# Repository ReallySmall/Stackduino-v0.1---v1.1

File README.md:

Stackduino
==========
Please visit the project site for details: https://www.stackduino.net

Copyright 2017 Richard Iles

Permission is hereby granted, free of charge, to any person obtaining a copy of this software and associated documentation files (the "Software"), to deal in the Software without restriction, including without limitation the rights to use, copy, modify, merge, publish, distribute, sublicense, and/or sell copies of the Software, and to permit persons to whom the Software is furnished to do so, subject to the following conditions:

The above copyright notice and this permission notice shall be included in all copies or substantial portions of the Software.

THE SOFTWARE IS PROVIDED "AS IS", WITHOUT WARRANTY OF ANY KIND, EXPRESS OR IMPLIED, INCLUDING BUT NOT LIMITED TO THE WARRANTIES OF MERCHANTABILITY, FITNESS FOR A PARTICULAR PURPOSE AND NONINFRINGEMENT. IN NO EVENT SHALL THE AUTHORS OR COPYRIGHT HOLDERS BE LIABLE FOR ANY CLAIM, DAMAGES OR OTHER LIABILITY, WHETHER IN AN ACTION OF CONTRACT, TORT OR OTHERWISE, ARISING FROM, OUT OF OR IN CONNECTION WITH THE SOFTWARE OR THE USE OR OTHER DEALINGS IN THE SOFTWARE.

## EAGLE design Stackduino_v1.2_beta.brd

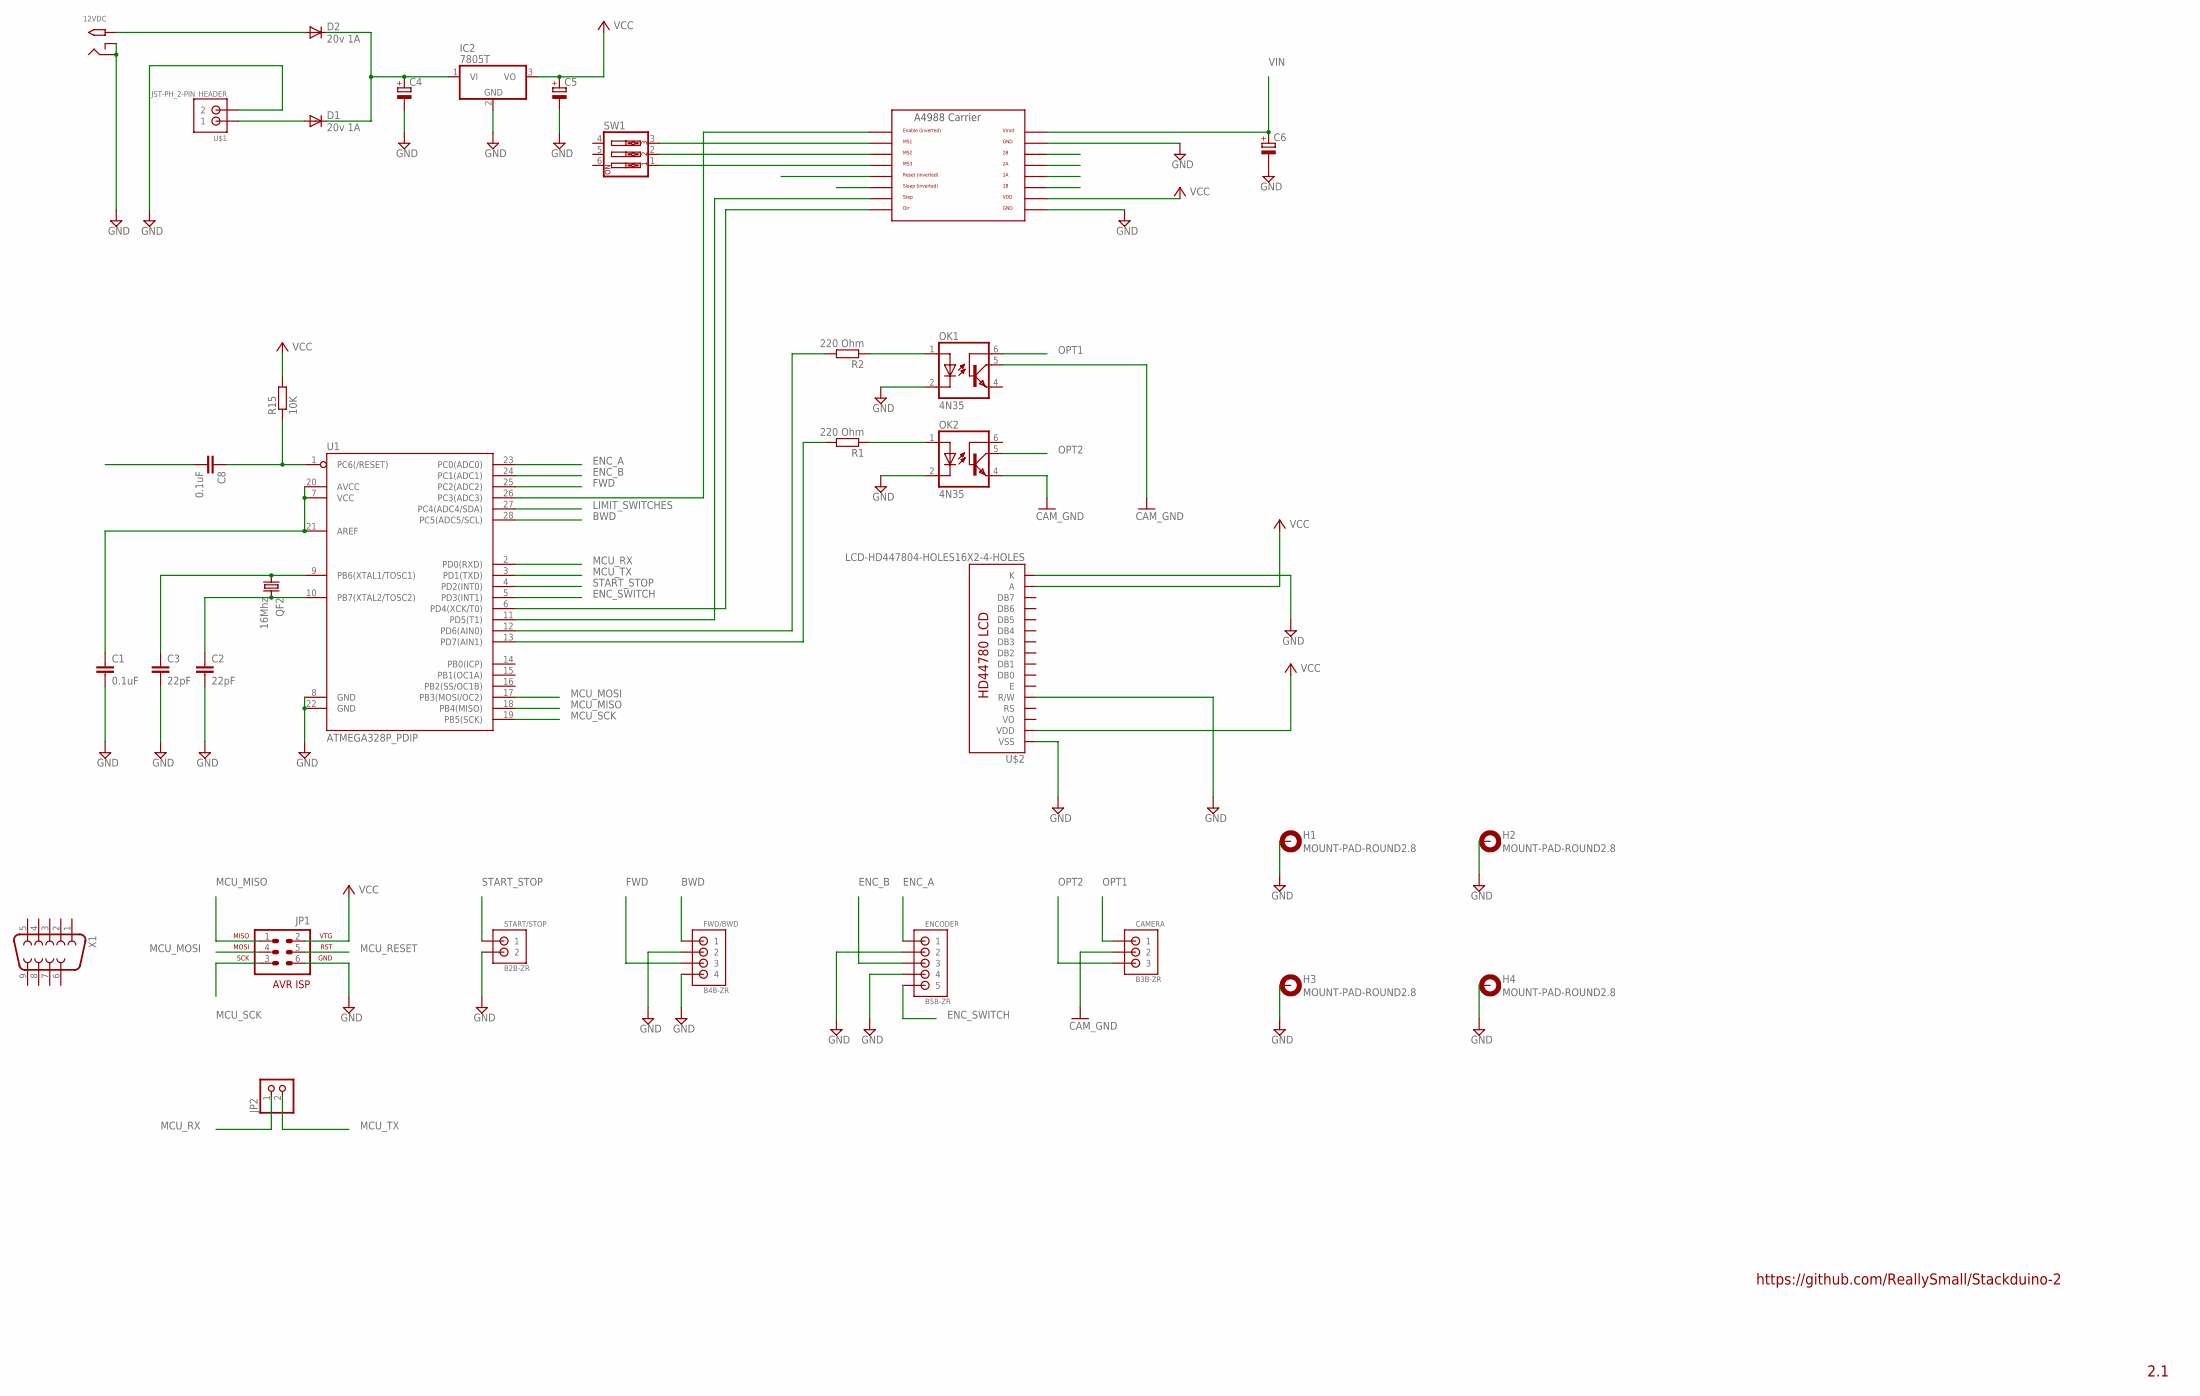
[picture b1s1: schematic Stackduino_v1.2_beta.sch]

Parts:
12VDC: 2.1MMJACKTHM; PJ-102A
A4988_CARRIER: A4988BREAKOUT
C1, C8: 0.1uF; C025-030X050
C2, C3: 22pF; C025-030X050
C4, C5, C6: CPOL-EUSANYO_C; SANYO-OSCON_C
CAMERA: B3B-ZR
D1, D2: 20v 1A; DO41-10
ENCODER: B5B-ZR
FWD/BWD: B4B-ZR
H1, H2, H3, H4: MOUNT-PAD-ROUND2.8; 2,8-PAD
IC2: 7805T; TO220H
JP1: AVR-5_AVR-ISP-6
JP2: PINHD-1X2; 1X02
OK1, OK2: 4N35; DIL06
QF2: 16Mhz; HC49U-V
R1, R2: 220 Ohm; 0207/10
R15: 10K; 0207/10
START/STOP: B2B-ZR
SW1: SW_DIP-3; EDG-03
U1: ATMEGA328P_PDIP; DIL28-3
U$1: JST-PH_2-PIN_HEADER; JST_B2B-PH_HEADER
U$2: LCD-HD447804-HOLES16X2-4-HOLES; LCD-16X2-4HOLES
X1: F09H

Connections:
BWD: FWD/BWD.1, U1.28 (PC5(ADC5/SCL))
CAM_GND: CAMERA.2, OK1.5 (COL), OK2.4 (EMI)
DIR: A4988_CARRIER.DIR, U1.6 (PD4(XCK/T0))
ENABLE: A4988_CARRIER.EN, U1.26 (PC3(ADC3))
ENC_A: ENCODER.1, U1.23 (PC0(ADC0))
ENC_B: ENCODER.3, U1.24 (PC1(ADC1))
ENC_SWITCH: ENCODER.5, U1.5 (PD3(INT1))
FWD: FWD/BWD.3, U1.25 (PC2(ADC2))
GND: 12VDC.RING, 12VDC.RING_SW, A4988_CARRIER.GND, A4988_CARRIER.GND@0 (GND), C1.2, C2.2, C3.2, C4.-, C5.-, C6.-, ENCODER.2, ENCODER.4, FWD/BWD.2, FWD/BWD.4, H1.B2,8, H2.B2,8, H3.B2,8, H4.B2,8, IC2.2 (GND), JP1.6, OK1.2 (C), OK2.2 (C), START/STOP.2, U1.8 (GND), U1.22 (GND), U$1.P2 (2), U$2.1 (VSS), U$2.5 (R/W), U$2.16 (K)
LIMIT_SWITCHES: U1.27 (PC4(ADC4/SDA))
MCU_MISO: JP1.1, U1.18 (PB4(MISO))
MCU_MOSI: JP1.4, U1.17 (PB3(MOSI/OC2))
MCU_RESET: C8.1, JP1.5, R15.1, U1.1 (PC6(/RESET))
MCU_RX: JP2.1, U1.2 (PD0(RXD))
MCU_SCK: JP1.3, U1.19 (PB5(SCK))
MCU_TX: JP2.2, U1.3 (PD1(TXD))
MS1: A4988_CARRIER.MS1, SW1.3
MS2: A4988_CARRIER.MS2, SW1.2
MS3: A4988_CARRIER.MS3, SW1.1
unnamed: D1.A, U$1.P1 (1)
unnamed: C1.1, U1.7 (VCC), U1.20 (AVCC), U1.21 (AREF)
unnamed: 12VDC.TIP, D2.A
unnamed: C2.1, QF2.2, U1.10 (PB7(XTAL2/TOSC2))
unnamed: C3.1, QF2.1, U1.9 (PB6(XTAL1/TOSC1))
unnamed: OK1.1 (A), R2.1
unnamed: OK2.1 (A), R1.1
OPT1: CAMERA.1, OK1.6 (BAS)
OPT2: CAMERA.3, OK2.5 (COL)
OUT1A: A4988_CARRIER.1B
OUT1B: A4988_CARRIER.1A
OUT2A: A4988_CARRIER.2A
OUT2B: A4988_CARRIER.2B
SLEEP: A4988_CARRIER.SLP (SLEEP)
START_STOP: START/STOP.1, U1.4 (PD2(INT0))
STEP: A4988_CARRIER.STEP, U1.11 (PD5(T1))
VCC: A4988_CARRIER.VDD, C5.+, IC2.3 (VO), JP1.2, R15.2, U$2.2 (VDD), U$2.15 (A)
VIN: A4988_CARRIER.VMOT, C4.+, C6.+, D1.C, D2.C, IC2.1 (VI)

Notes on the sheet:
https://github.com/ReallySmall/Stackduino-2
2.1

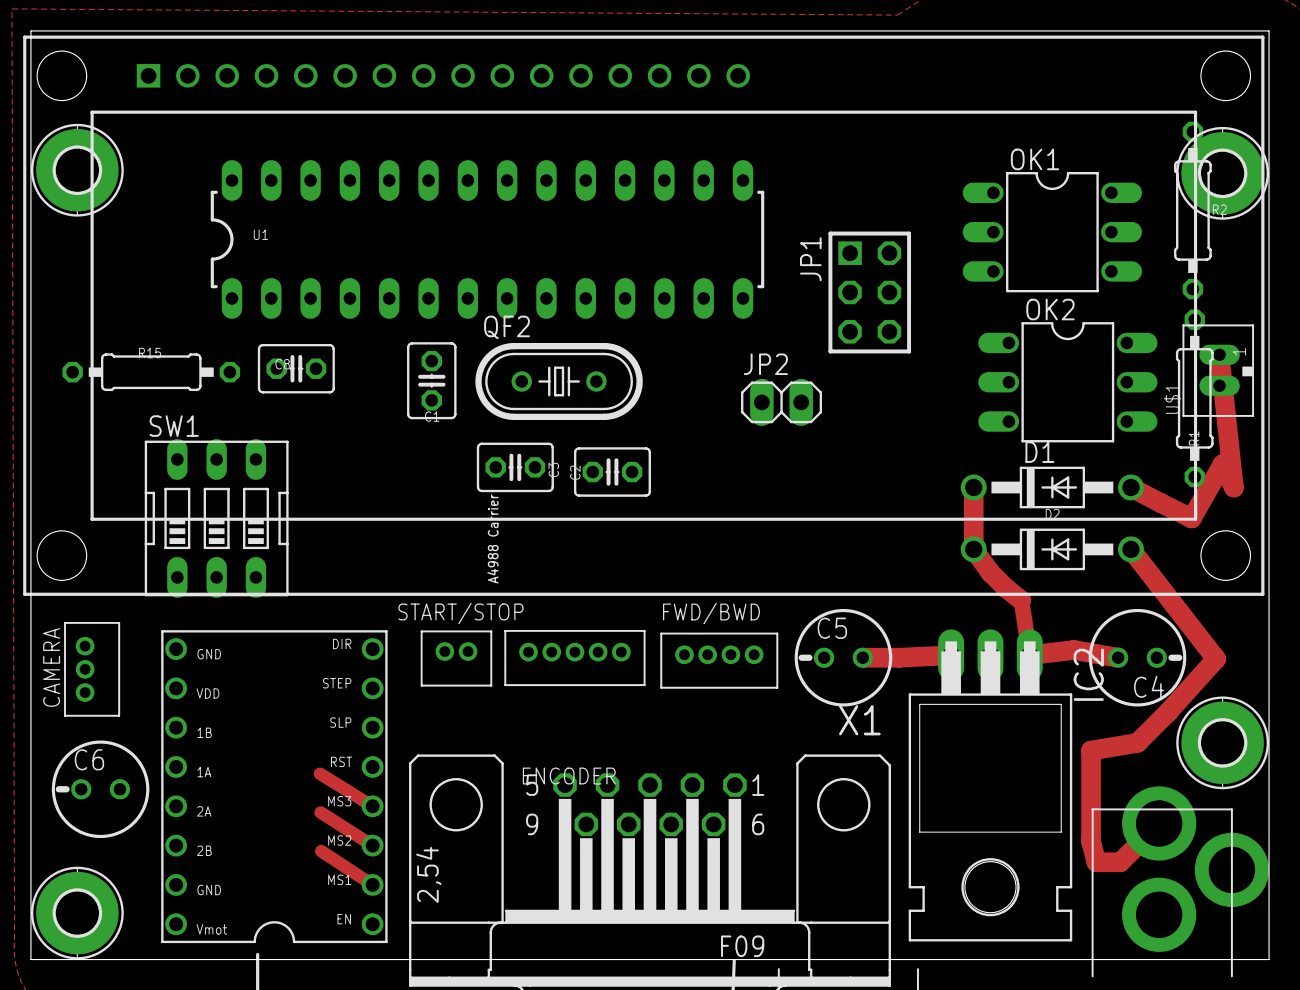
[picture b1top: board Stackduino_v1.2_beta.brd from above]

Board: 2 copper layers, 80.0 x 60.0 mm, 33 parts (0 on the bottom side), 31 nets.

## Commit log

2013-03-03 First commit of Stackduino sketch
2013-03-03 Amended title
2013-03-03 added Fritzing wiring diagram
2013-03-03 added Flickr link
2013-03-03 Chnaged file name
2013-03-03 Create gh-pages branch via GitHub
2013-06-27 added digitalToggle
2013-06-27 Added Digital Toggle Library
2013-06-27 Removed duplicate
2013-06-30 Discontinued control method
2013-06-30 Removed old files
2013-10-12 Changed folder name
2013-10-12 Changed filename
2013-10-12 Updated direction code to match wiring of pcb
2013-11-09 Added gereber files for Stackduino v1.1
2013-11-09 Added pcb diagram
2013-11-09 150 images, 14 micron spacing
2013-11-10 Enabled option to disable Easydriver
    ...when not stepping. Runs a lot cooler and uses less power
2013-11-10 Added note on Easydriver disable
2013-11-10 Amended link
2013-11-12 added pcb component labels
2013-11-12 Added silkscreen labels
2013-11-13 Added component list
2013-11-13 Added note on FT232RL adapter pinout
2013-11-13 Removed un-needed line
2013-11-17 Added HDR bracketing support
    Stackduino can take a selectable multiple of images per focus slice to
    support exposure bracketing
2013-11-17 Adjusted features list formatting
2013-11-17 A sprinkle of optimisations
2013-11-17 Added commenting
2013-11-17 Created new project homepage
2013-12-07 Substituted description for link to project page
2013-12-19 deleted webpage files from main branch
    Pleaseenter the commit message for your changes. Lines starting
2013-12-19 Fixed library file for compat with new IDE
2014-02-01 Added image of populated pcb
2014-02-01 Removed duplicated sentence
2014-02-01 Ammended wording
2014-02-02 Responsive images
2014-02-02 responsive image captions
2014-07-13 Overhauled sketch
    - no longer requires the DigitalToggle library
    - screen updates are done more effeciently, only when variables are
    changed - and the check is now done once diectly within the encoder
    reading function, rather than individually within each menu item
    - due to more efficient screen updates, lcd.clear can now be used before
    each update, so padding out strings to fill lcd rows is no longer
2014-07-13 minor content amends to project homepage
2014-07-13 another minor content tweak
2014-07-13 tweaks to mirror lockup sequence
2014-07-20 Started Stackduino v1.2 board in Eagle
2014-11-19 corrected error in component list
2014-11-19 reinstated correct sketch
    Woops!
2015-09-26 Fixed compile error in newest version of IDE
2016-11-20 Updated readme to point to project site
2016-11-20 Updated to point to project site
2017-01-08 Folder tidyup
2017-02-12 added missing c6 value - resolves #4
2017-09-16 fix overwriting of parent loop variable

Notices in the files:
parts and their libraries:
SparkFun-DigitalIC: Licensing: CC v3.0 Share-Alike You are welcome to use this library for commercial purposes.
